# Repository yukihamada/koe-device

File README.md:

<div align="center">

# Koe — Sound That Connects

**1 device remembers. 100 devices become an orchestra.**

**[Website](https://koe.live/)** · **[Koe Pro](https://koe.live/pro)** · **[Busker](https://koe.live/busker)** · **[Classroom](https://koe.live/classroom)** · **[Moji](https://koe.live/moji)** · **[SolunaOS](https://koe.live/soluna-os)**

**[日本語](README.ja.md)** · **[Documentation](https://koe.live/docs.html)**

</div>

---

## Products

### Hardware

| Device | Description | Key Specs | BOM | Target Price |
|--------|-------------|-----------|-----|-------------|
| **Koe Pro** | Ultra-low latency wireless audio transmitter for musicians | ESP32-S3 + DW3000 UWB, 48kHz/24bit, <15ms | ~$35 | $199 |
| **Koe Hub** | Real-time mixer & streaming server | Pi CM5, 8-channel, EQ/reverb/comp, SRT/RTMP | ~$120 | $399 |
| **COIN** | Personal audio device for crowds | ESP32-S3, Soluna P2P sync, 26mm disc | ~$24 | $65 |
| **COIN Lite** | Receive-only festival device | ESP32-C3, minimal BOM | ~$6 | $29 |
| **Koe Seed** | Auracast receiver, 5 form factors | nRF5340 + nRF21540, 28mm PCB, Find My tracker | ~$8.30 | $35 |
| **FILL** | Powered speaker | Pi CM5 + 50W Class-D amp, 8" + 1" horn | — | $1,500 |
| **STAGE** | Festival bridge | Pi CM5, GPS sync, PA routing | — | $800 |
| **SUB** | Subwoofer | 15", 1000W | — | $1,200 |

### Software

| App | Description | URL |
|-----|-------------|-----|
| **Busker** | Street performance: audience phones become wireless speakers + tip jar | [koe.live/busker](https://koe.live/busker) |
| **Classroom** | Teacher/guide voice to everyone's earphones, no app needed | [koe.live/classroom](https://koe.live/classroom) |
| **Moji** | Real-time speech translation (JA/EN/ZH/KO/ES/FR) | [koe.live/moji](https://koe.live/moji) |
| **SolunaOS** | Festival management dashboard (timeline, LED show, routing, tickets) | [koe.live/soluna-os](https://koe.live/soluna-os) |

## Architecture

```
[Instruments] --> [Koe Pro] --WiFi+UWB--> [Koe Hub]
[Phones]      --> [Busker/Classroom] -->    |-> STAGE -> FILL -> SUB (PA)
[Voice]       --> [Moji]            -->    |-> COIN / COIN Lite (crowd)
                                           |-> SRT/RTMP (stream)
                                           +-> SolunaOS (management)
```

## Latency

| Path | Latency |
|------|---------|
| Koe Pro -> Hub -> PA | ~14ms |
| Phone -> Busker/Classroom | ~50ms (WebRTC) |
| Soluna crowd sync | ~110ms |
| Moji translation | ~800ms |

## Koe Seed — One PCB, Five Form Factors

The Seed uses a single 28mm round PCB (nRF5340 + nRF21540) that fits in five different enclosures:

| Form Factor | Case | Use Case |
|-------------|------|----------|
| **Wristband** | 35x30x12mm oval pod | Festivals, concerts — slides into silicone band |
| **Keychain** | 32mm disc, 10mm thick | Everyday carry, keys, bag |
| **Clip-On** | 35x25x12mm + spring clip | Backpack strap, belt loop, pocket edge |
| **Badge** | 55x35x8mm rectangle | Conferences, museum tours, corporate events |
| **Pendant** | 35x28x10mm teardrop | Guided tours, jewelry — wear on cord |

Additional ultra-thin option: **Sticker** (32mm, 6mm thick) — stick on phone, laptop, helmet.

### Built-in Tracker (Find My Compatible)

Every Seed broadcasts an [OpenHaystack](https://github.com/seemoo-lab/openhaystack)-compatible BLE beacon in parallel with Auracast reception. This enables lost-item tracking via Apple's Find My network:

- Broadcasts every 2 seconds (~0.01mA power impact)
- Public key rotates every 15 minutes for privacy
- Any nearby iPhone relays the encrypted location to Apple's servers
- Owner retrieves location via the OpenHaystack macOS app

This runs **always** (even during audio playback) using a secondary BLE advertising set on the nRF5340.

## Directory Structure

```
koe-device/
├── docs/                    # Website (koe.live, served by Fly.io)
│   ├── index.html           # Landing page
│   ├── pro.html             # Koe Pro + Hub product page
│   ├── busker.html          # Busker mode
│   ├── classroom.html       # Classroom mode
│   ├── moji.html            # Real-time translation
│   ├── soluna-os.html       # Festival dashboard
│   ├── app/                 # P2P web app (Soluna)
│   └── images/              # Product renders
├── firmware/                # ESP32-S3 Rust firmware
│   ├── src/
│   │   ├── main.rs          # Entry point, dual mode (Koe/Soluna)
│   │   ├── audio.rs         # I2S, VAD, DSP
│   │   ├── pro.rs           # Koe Pro low-latency transmitter
│   │   ├── uwb.rs           # DW3000 UWB clock sync
│   │   ├── soluna.rs        # UDP multicast P2P protocol
│   │   ├── cloud.rs         # HTTPS to chatweb.ai
│   │   └── led.rs           # WS2812B status LED
│   ├── coin-lite/           # COIN Lite (ESP32-C3) firmware
│   └── demo/                # Minimal sync demo (2 boards)
├── hub/                     # Koe Hub software (Pi CM5, Rust)
├── server/                  # koe.live Axum server (static + OTA API)
├── hardware/
│   ├── kicad/               # Schematic + PCB
│   └── bom/                 # Bill of materials
├── manufacturing/           # JLCPCB BOM/CPL
├── regulatory/              # Regulatory docs (技適 etc.)
├── enclosure/               # 3D printable cases
├── tools/                   # guitar-stream.py, led-send.py, led-show.py
└── stage/                   # STAGE device software
```

## Quick Start

### Firmware (ESP32-S3)

```bash
# Install toolchain
cargo install espup && espup install
cargo install espflash ldproxy

# Build
cd firmware && cargo build --release

# Flash
cargo espflash flash --release --monitor
```

### Hub (Pi CM5)

```bash
cd hub && cargo run --release
# Dashboard: http://localhost:3000
```

### COIN Lite (ESP32-C3)

```bash
cd firmware/coin-lite && cargo build --release
```

### Deploy Site

```bash
fly deploy --remote-only -a koe-live
```

### OTA Firmware Update

```bash
cd firmware
./deploy-ota.sh --release --token $KOE_ADMIN_TOKEN
```

## Protocols

### Soluna (crowd sync)

- UDP multicast `239.42.42.1:4242`
- IMA-ADPCM 4:1 compression, 16kHz mono
- NTP + GPS time sync
- WebSocket bridge at `wss://koe.live/ws/soluna`

### Koe Pro (low-latency)

- UDP unicast port 4244
- PCM24 48kHz, 128-sample buffer
- UWB (DW3000) sub-microsecond clock sync
- WebRTC signaling at `wss://koe.live/ws/signal`

## Links

- **Website:** https://koe.live/
- **Koe Software:** https://app.koe.live
- **GitHub:** https://github.com/yukihamada/koe-device
- **EnablerDAO:** https://github.com/enablerdao

## License

MIT — see [LICENSE](LICENSE)

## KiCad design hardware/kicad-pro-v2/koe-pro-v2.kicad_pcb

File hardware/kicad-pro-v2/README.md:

# Koe Pro v2 --- KiCad Project

nRF5340 + DW3720 UWB, 45x30mm 4-layer PCB.

## Open in KiCad
1. Install KiCad 8.0+
2. Open koe-pro-v2.kicad_pro
3. Install Nordic lib: Plugin Manager -> Add repo -> https://raw.githubusercontent.com/hlord2000/hlord2000-kicad-repository/main/repository.json

## Generate Manufacturing Files
1. Plot -> Gerber (F.Cu, B.Cu, In1.Cu, In2.Cu, F.Mask, B.Mask, F.SilkS, Edge.Cuts)
2. Drill -> Excellon
3. BOM -> KiCad BOM plugin
4. CPL -> Fabrication Outputs -> Footprint Position

## JLCPCB Order
1. Upload Gerber ZIP
2. Select 4-layer, 1.6mm, FR-4, HASL
3. Upload BOM + CPL for SMT assembly

## Key ICs
| Ref | Part | Function |
|-----|------|----------|
| U1 | nRF5340-QKAA | BLE 5.3 MCU (dual-core M33) |
| U2 | DW3720 | UWB transceiver |
| U3 | AK5720 | 24-bit ADC |
| U4 | PCM5102A | 32-bit DAC |
| U5 | MAX98357A | I2S speaker amp |
| U6 | nPM1300 | PMIC (LiPo charger + buck) |

## BOM Cost
~$23.05 per board (JLCPCB SMT assembly)

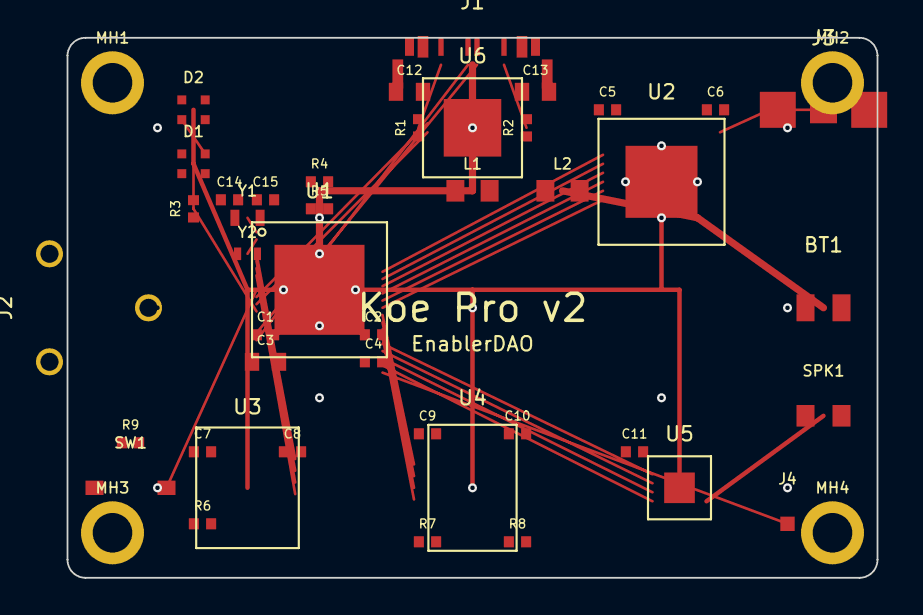
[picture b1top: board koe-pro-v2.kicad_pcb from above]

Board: 4 copper layers, 45.0 x 30.0 mm, 47 parts (0 on the bottom side), 10 nets.

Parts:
BT1: LiPo_800mAh; JST_PH_S2B-PH-K_1x02_P2.00mm_Horizontal
C1, C2, C5, C7, C9: 100nF; C_0402_1005Metric
C3, C12: 10uF; C_0603_1608Metric
C4: 1uF; C_0402_1005Metric
C6: 10nF; C_0402_1005Metric
C8, C10, C11: 10uF; C_0402_1005Metric
C13: 22uF; C_0603_1608Metric
C14, C15: 12pF; C_0402_1005Metric
D1, D2: WS2812B; LED_WS2812B-2020_PLCC4_2.0x2.0mm
J1: USB-C; USB_C_Receptacle_USB2.0
J2: PJ-320A; AudioJack3_SJ_CUI_SJ-3523-SMT
J3: SMA_UWB; SMA_Amphenol_132289_EdgeMount
J4: BLE_ANT; Texas_SWRA117D_2.4GHz_Right
L1: 10uH; L_0805_2012Metric
L2: 4.7uH; L_0805_2012Metric
MH1, MH2, MH3, MH4: M2; MountingHole_2.2mm_M2_Pad
R1, R2: 5.1k; R_0402_1005Metric
R3: 330R; R_0402_1005Metric
R4, R5: 4.7k; R_0402_1005Metric
R6, R7, R8, R9: 10k; R_0402_1005Metric
SPK1: Speaker; PinHeader_1x02_P2.54mm_Vertical
SW1: BTN; SW_SPST_CK_RS282G05A3
U1: nRF5340-QKAA; QFN-94-1EP_7x7mm_P0.4mm
U2: DW3720; QFN-48-1EP_6.5x6.5mm_P0.5mm
U3: AK5720VT; SSOP-16_5.3x6.2mm_P0.65mm
U4: PCM5102A; TSSOP-20_4.4x6.5mm_P0.65mm
U5: MAX98357A; QFN-16-1EP_3x3mm_P0.5mm
U6: nPM1300; QFN-32-1EP_5x5mm_P0.5mm
Y1: 32MHz; Crystal_SMD_2012-2Pin_2.0x1.2mm
Y2: 32.768kHz; Crystal_SMD_1610-2Pin_1.6x1.0mm

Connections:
+3V3: C1.1, C2.1, C3.1, C4.1, C5.1, C6.1, C7.1, C8.1, C9.1, C10.1, C11.1, C13.1, D1.1, D2.1, L1.2, L2.2, R4.1, R5.1, R9.1
+VBAT: BT1.1, L2.1
+VBUS: C12.1, J1.V1, J1.V2
BTN: R9.2, SW1.1
CC1: J1.CC1, R1.1
CC2: J1.CC2, R2.1
GND: BT1.2, C1.2, C2.2, C3.2, C4.2, C5.2, C6.2, C7.2, C8.2, C9.2, C10.2, C11.2, C12.2, C13.2, C14.2, C15.2, D1.3, D2.3, J1.G1, J1.G2, J1.S1, J1.S2, J2.3, J3.2, J3.3, MH1.1, MH2.1, MH3.1, MH4.1, R1.2, R2.2, R6.1, R7.1, R8.1, SW1.2, U1.95, U2.49, U5.17, U6.33
LED_DATA: D1.2, R3.1
XTAL_32M_1: C14.1, Y1.1
XTAL_32M_2: C15.1, Y1.2

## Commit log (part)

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2026-03-18 Rename site/ to docs/ for GitHub Pages
2026-03-18 Fix GitHub links: tree/main → tree/master
2026-03-18 Expand open-source grid to 3x2: add form factors + KiCad
2026-03-18 Create CNAME
2026-03-18 Update BUY_NOW: 4-phase plan, Coin () + Lantern STAGE ()
2026-03-18 Add FILL-DESIGN.md: sealed 15L, FIR crossover, ES9038Q2M, WiFi 7 AP for 500+ devices
2026-03-18 Fix: COIN has no GPS — correct all references to SUB/FILL only
2026-03-18 Switch to Fly.io: SSL working, remove GitHub Pages CNAME
2026-03-18 Migrate koe.elio.love → app.koe.live with 301 redirect
2026-03-24 BLE: アドバタイズデータにデバイス名+UUID FFE0を明示設定
2026-03-26 Fix splash z-index + full UI redesign: deep black, spatial audio glow, waveform visualizer
2026-05-04 ci: add GitHub Actions deploy workflow
    Auto-deploy to Fly.io on push to main
2026-05-04 analytics: add enabler-analytics tracking to all HTML pages
2026-05-04 ci: add Claude Code agent workflow (issue → implement → PR)
2026-05-18 build(deps): bump openssl from 0.10.76 to 0.10.80 in /server
    Bumps [openssl](https://github.com/rust-openssl/rust-openssl) from 0.10.76 to 0.10.80.
    - [Release notes](https://github.com/rust-openssl/rust-openssl/releases)
    - [Commits](https://github.com/rust-openssl/rust-openssl/compare/openssl-v0.10.76...openssl-v0.10.80)
    ---
    updated-dependencies:
    - dependency-name: openssl
2026-05-18 build(deps): bump rand from 0.8.5 to 0.8.6 in /server
    Bumps [rand](https://github.com/rust-random/rand) from 0.8.5 to 0.8.6.
    - [Release notes](https://github.com/rust-random/rand/releases)
    - [Changelog](https://github.com/rust-random/rand/blob/0.8.6/CHANGELOG.md)
    - [Commits](https://github.com/rust-random/rand/compare/0.8.5...0.8.6)
    ---
    updated-dependencies:
2026-05-18 chore(deps): add Dependabot weekly version updates
2026-05-18 chore(deps): bump rustls-webpki from 0.103.10 to 0.103.13 in /server
    Bumps [rustls-webpki](https://github.com/rustls/webpki) from 0.103.10 to 0.103.13.
    - [Release notes](https://github.com/rustls/webpki/releases)
    - [Commits](https://github.com/rustls/webpki/compare/v/0.103.10...v/0.103.13)
    ---
    updated-dependencies:
    - dependency-name: rustls-webpki
2026-06-10 chore(deps): bump openssl from 0.10.76 to 0.10.80 in /hub
    Bumps [openssl](https://github.com/rust-openssl/rust-openssl) from 0.10.76 to 0.10.80.
    - [Release notes](https://github.com/rust-openssl/rust-openssl/releases)
    - [Commits](https://github.com/rust-openssl/rust-openssl/compare/openssl-v0.10.76...openssl-v0.10.80)
    ---
    updated-dependencies:
    - dependency-name: openssl
2026-06-10 chore(deps): bump esp-rs/xtensa-toolchain from 1.5 to 1.7
    Bumps [esp-rs/xtensa-toolchain](https://github.com/esp-rs/xtensa-toolchain) from 1.5 to 1.7.
    - [Release notes](https://github.com/esp-rs/xtensa-toolchain/releases)
    - [Commits](https://github.com/esp-rs/xtensa-toolchain/compare/v1.5...v1.7)
    ---
    updated-dependencies:
    - dependency-name: esp-rs/xtensa-toolchain
2026-06-10 chore(deps): bump actions/checkout from 5 to 6
    Bumps [actions/checkout](https://github.com/actions/checkout) from 5 to 6.
    - [Release notes](https://github.com/actions/checkout/releases)
    - [Changelog](https://github.com/actions/checkout/blob/main/CHANGELOG.md)
    - [Commits](https://github.com/actions/checkout/compare/v5...v6)
    ---
    updated-dependencies:
2026-06-22 chore(deps): bump actions/checkout from 5 to 7
    Bumps [actions/checkout](https://github.com/actions/checkout) from 5 to 7.
    - [Release notes](https://github.com/actions/checkout/releases)
    - [Changelog](https://github.com/actions/checkout/blob/main/CHANGELOG.md)
    - [Commits](https://github.com/actions/checkout/compare/v5...v7)
    ---
    updated-dependencies:
